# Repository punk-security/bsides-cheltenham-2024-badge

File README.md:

# bsides-cheltenham-2024-badge
The UFO badge for BSIDES Cheltenham 2024!

Lots of things in this repo:

- eagle-files: all the stuff you need to tinker and modify the PCB
- gerber-files.zip: the file you can upload to JLCPCB and order your own badge, as is
- 3d_printed_case.stl: a cool little push fit case you can print
- bsides-cheltenham-2024-badge.ino: the arduino code that powers the badge, which you can modify and flash via the SAO connector
- ufo.svg: the original vector design for the badge
- morse_code_instructional_booklet.pdf: the flyer we gave out on the day with the codes and instructions

## Bill Of Materials

You can see a parts list on DigiKey [here](https://www.digikey.co.uk/en/mylists/list/Z9CH9C1GM3)

Essentially its:

* ATTINY402 microcontroller 
* Button - any surface mount button fitting the footprint will work
* CR2032 battery clip - surface mount not through hole
* Neopixel 5050 addressable LED - Definitely get the right version of these

## Eagle designs and ordering your own badge

We've uploaded the AutoCAD EAGLE schematic, board design and custom footprints so you can make your own variants!  You will probably have to do some tweaks to get it working as they're not designed to be standalone exports.

We've also uploaded the gerber_files.zip.  Take this to JLCPCB and you can order your own exact copies of the board :)

## Writing and flashing code!

We use [MegaTinyCore](https://github.com/SpenceKonde/megaTinyCore) for the arduino interface for ATTINY4x2 chips.

Dev and flashing is done within the Arduino IDE ( < v2 ) using a jtag2updi interface, as discussed [here](https://github.com/SpenceKonde/AVR-Guidance/blob/master/UPDI/jtag2updi.md)

We use [these little usb sticks](https://amzn.eu/d/c0lx0wG), with a 4.7k resistor soldered between the Tx and Rx lines.  

### Installing MegaTinyCore dependencies

This board package can be installed via the board manager in arduino. The boards manager URL is:

`http://drazzy.com/package_drazzy.com_index.json`

1. File -> Preferences, enter the above URL in "Additional Boards Manager URLs"
2. Tools -> Boards -> Boards Manager...
3. Wait while the list loads (takes longer than one would expect, and refreshes several times).
4. Select "megaTinyCore by Spence Konde" and click "Install". For best results, choose the most recent version.

### Setting up the IDE

1. Open the file **bsides-cheltenham-2024-badge.ino** in arduino
2. Select tools > Board > megaTinyCore > ATtiny412/402/212/202
3. Select tools > Chip > ATtiny402
4. Select tools > Clock > 8Mhz internal *(we get power issues otherwise)*
5. Select tools > Programmer > SerialUPDI SLOW
6. Select tools > Port > ( pick your COM port)

### Flashing firmware
1. Connect the 3v3 pin to 3v on your usb (maybe wedge it in the battery clip)
2. Connect GND to GND
3. Connect UPDI to the RxD port
4. Click Upload button

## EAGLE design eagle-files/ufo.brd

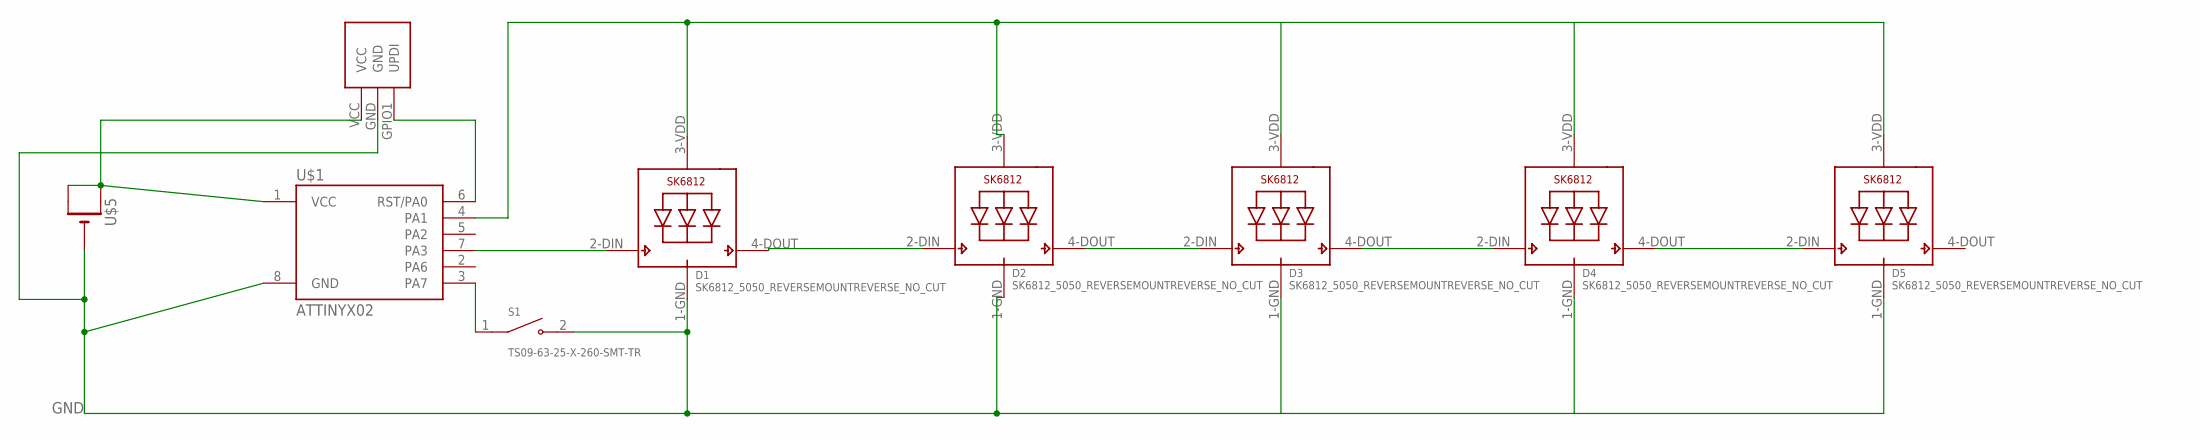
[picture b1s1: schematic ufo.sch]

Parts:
D1, D2, D3, D4, D5: SK6812_5050_REVERSEMOUNTREVERSE_NO_CUT; SK6812_REVERSE_NO_CUT
S1: TS09-63-25-X-260-SMT-TR; SW_TS09-63-25-X-260-SMT-TR
U$1: ATTINYX02; SOIC08_JEDEC_150MIL
U$2: SAO; SAO_SMD
U$5: CR2032SMT; CR2032-SMD

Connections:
GND: D1.1-GND (GND), D2.1-GND (GND), D3.1-GND (GND), D4.1-GND (GND), D5.1-GND (GND), S1.2, U$1.8 (GND), U$2.GND, U$5.-
unnamed: D1.4-DOUT (DO), D2.2-DIN (DI)
unnamed: D1.2-DIN (DI), U$1.7 (PA3)
unnamed: D3.4-DOUT (DO), D4.2-DIN (DI)
unnamed: D2.4-DOUT (DO), D3.2-DIN (DI)
unnamed: S1.1, U$1.3 (PA7)
unnamed: D4.4-DOUT (DO), D5.2-DIN (DI)
unnamed: U$1.6 (RST/PA0), U$2.GPIO1 (UPDI)
VCC1: U$1.1 (VCC), U$2.VCC, U$5.+$1 (+), U$5.+$2 (+1)
VDD1: D1.3-VDD (VDD), D2.3-VDD (VDD), D3.3-VDD (VDD), D4.3-VDD (VDD), D5.3-VDD (VDD), U$1.4 (PA1)

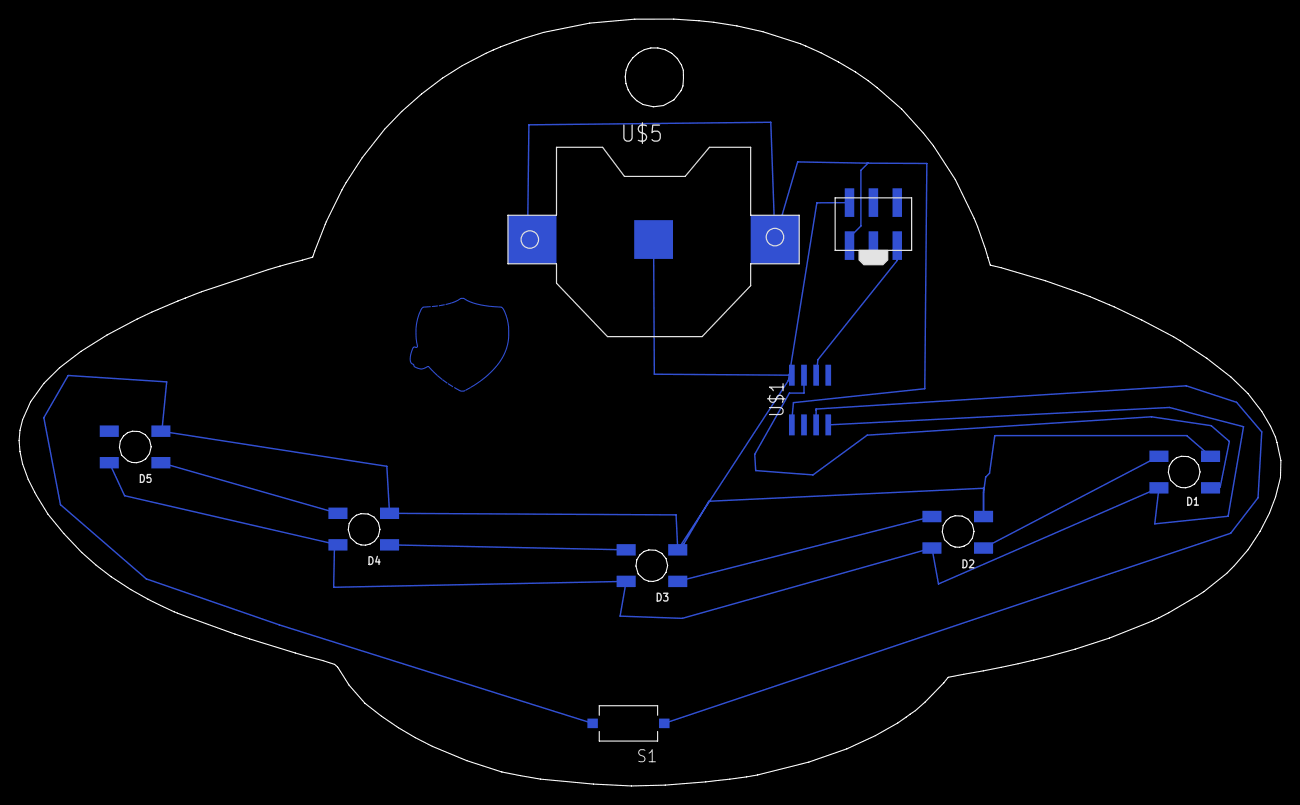
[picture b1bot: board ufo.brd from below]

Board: 2 copper layers, 132.1 x 80.3 mm, 9 parts (9 on the bottom side), 10 nets.

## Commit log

2024-05-30 feat: init
2024-05-30 add repo content notes
